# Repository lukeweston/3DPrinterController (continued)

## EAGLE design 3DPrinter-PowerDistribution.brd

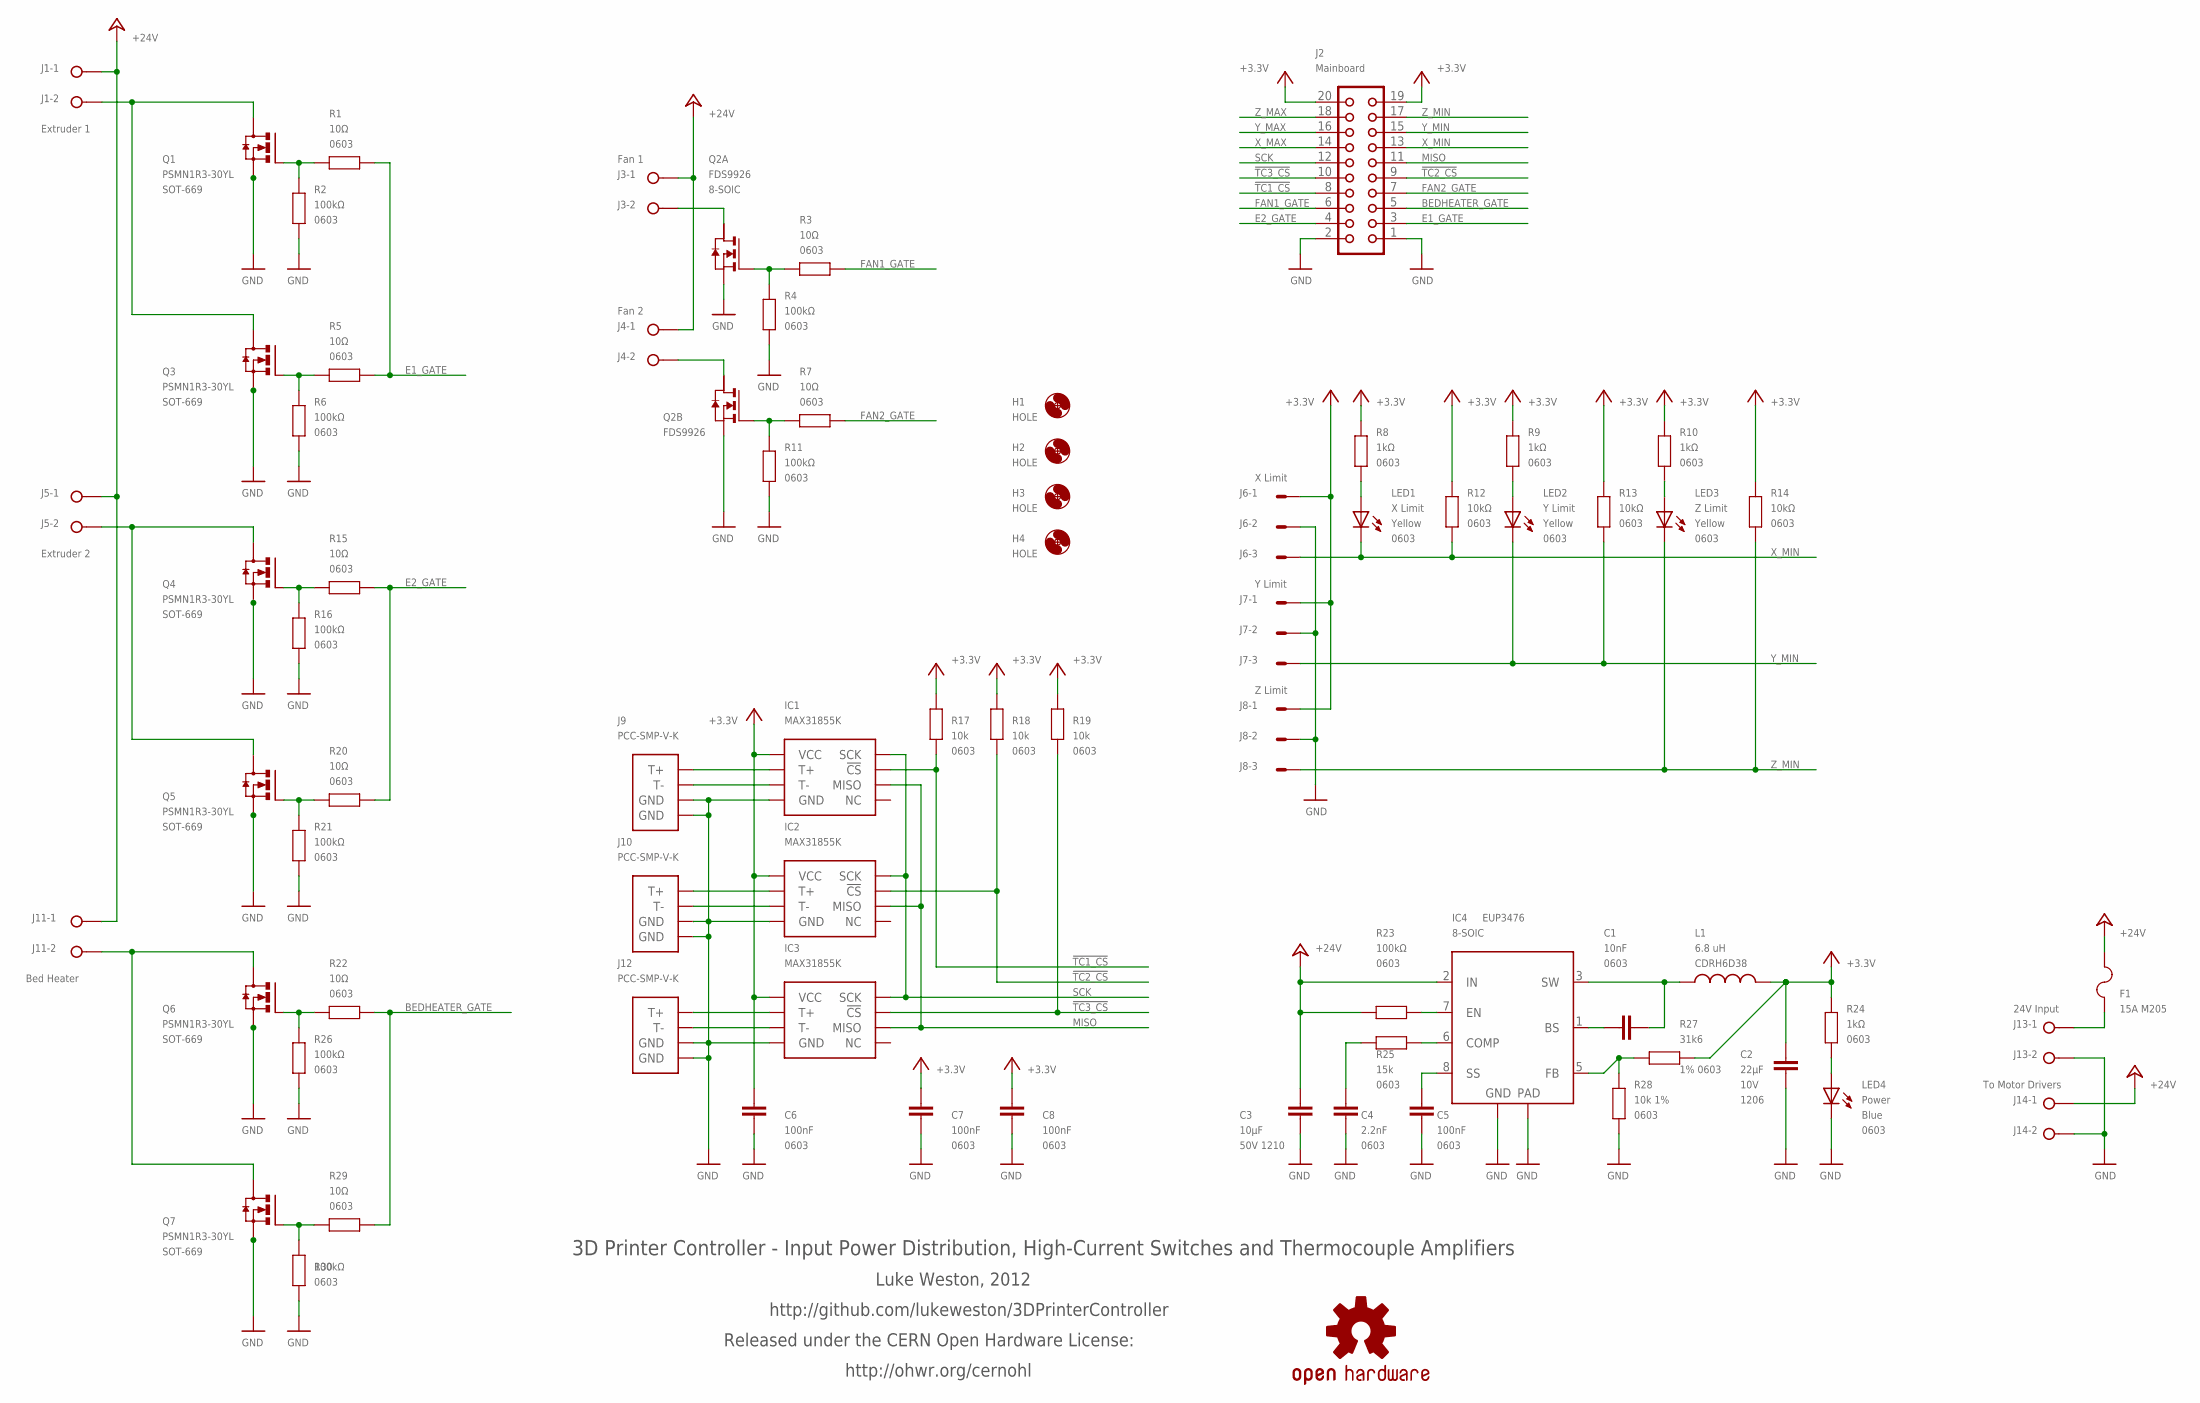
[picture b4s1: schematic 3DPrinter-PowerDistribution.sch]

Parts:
C1: 10nF; 0603
C2: 22µF; C1206K; VOLTAGE 10V
C3: 10µF; C1210K; VOLTAGE 50V 1210
C4: 2.2nF; 0603
C5, C6, C7, C8: 100nF; 0603
F1: 15A M205; SHK20L
H1, H2, H3, H4: HOLE; 3,2
IC1, IC2, IC3: MAX31855K; MCLENG_SOIC-8
IC4: EUP3476; SO08T
J1: Extruder 1; W237-132
J2: Mainboard; CON20L
J3: Fan 1; W237-132
J4: Fan 2; W237-132
J5: Extruder 2; W237-132
J6: X Limit; 7395-03
J7: Y Limit; 7395-03
J8: Z Limit; 7395-03
J9, J10, J12: PCC-SMP-V-K; MCLAUGHLINENG_TC_JACK
J11: Bed Heater; W237-132
J13: 24V Input; W237-132
J14: To Motor Drivers; W237-132
L1: 6.8 uH; CDRH
LED1: X Limit; LED-0603
LED2: Y Limit; LED-0603
LED3: Z Limit; LED-0603
LED4: Power; LED-0603
Q1, Q3, Q4, Q5, Q6, Q7: PSMN1R3-30YL; SOT669
Q2: FDS9926; SM8
R1, R3, R5, R7, R15, R20, R22, R29: 10Ω; 0603
R2, R4, R6, R11, R16, R21, R23, R26, R30: 100kΩ; 0603
R8, R9, R10, R24: 1kΩ; 0603
R12, R13, R14: 10kΩ; 0603
R17, R18, R19: 10k; 0603
R25: 15k; 0603
R27: 31k6; 0603
R28: 10k 1%; 0603
SY: OSHW-LOGOS; OSHW-LOGO-S

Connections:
!TC1_CS: IC1.CS (!CS), J2.8, R17.2
!TC2_CS: IC2.CS (!CS), J2.9, R18.2
!TC3_CS: IC3.CS (!CS), J2.10, R19.2
+3.3V: C2.1, C6.1, C7.1, C8.1, IC1.VCC, IC2.VCC, IC3.VCC, J2.19, J2.20, J6.1, J7.1, J8.1, L1.2, R8.1, R9.1, R10.1, R12.1, R13.1, R14.1, R17.1, R18.1, R19.1, R24.1, R27.1
+24V: C3.1, F1.2A (2), IC4.2 (IN), J1.1, J3.1, J4.1, J5.1, J11.1, J14.1, R23.2
BEDHEATER_GATE: J2.5, R22.1, R29.1
E1_GATE: J2.3, R1.1, R5.1
E2_GATE: J2.4, R15.1, R20.1
FAN1_GATE: J2.6, R3.1
FAN2_GATE: J2.7, R7.1
GND: C2.2, C3.2, C4.1, C5.1, C6.2, C7.2, C8.2, IC1.GND, IC2.GND, IC3.GND, IC4.4 (GND), IC4.9 (TGND), J2.1, J2.2, J6.2, J7.2, J8.2, J9.P$1 (GND), J9.P$2 (GND), J10.P$1 (GND), J10.P$2 (GND), J12.P$1 (GND), J12.P$2 (GND), J13.2, J14.2, LED4.C, Q1.1 (S), Q1.2 (S), Q1.3 (S), Q2.1 (S), Q2.3 (S), Q3.1 (S), Q3.2 (S), Q3.3 (S), Q4.1 (S), Q4.2 (S), Q4.3 (S), Q5.1 (S), Q5.2 (S), Q5.3 (S), Q6.1 (S), Q6.2 (S), Q6.3 (S), Q7.1 (S), Q7.2 (S), Q7.3 (S), R2.2, R4.2, R6.2, R11.2, R16.2, R21.2, R26.2, R28.2, R30.2
J5: J11.2, Q6.MB (D), Q7.MB (D)
MISO: IC1.SO (MISO), IC2.SO (MISO), IC3.SO (MISO), J2.11
unnamed: Q3.4 (G), R5.2, R6.1
unnamed: J1.2, Q1.MB (D), Q3.MB (D)
unnamed: Q4.4 (G), R15.2, R16.1
unnamed: J5.2, Q4.MB (D), Q5.MB (D)
unnamed: Q5.4 (G), R20.2, R21.1
unnamed: F1.1A (1), J13.1
unnamed: Q6.4 (G), R22.2, R26.1
unnamed: IC1.T+, J9.T+
unnamed: Q7.4 (G), R29.2, R30.1
unnamed: J3.2, Q2.5 (D)
unnamed: IC1.T-, J9.T-
unnamed: J4.2, Q2.7 (D)
unnamed: Q2.4 (G), R3.2, R4.1
unnamed: Q2.2 (G), R7.2, R11.1
unnamed: LED1.A, R8.2
unnamed: LED2.A, R9.2
unnamed: LED3.A, R10.2
unnamed: LED4.A, R24.2
unnamed: Q1.4 (G), R1.2, R2.1
unnamed: IC3.T-, J12.T-
unnamed: IC3.T+, J12.T+
unnamed: IC2.T-, J10.T-
unnamed: IC2.T+, J10.T+
unnamed: IC4.7 (EN), R23.1
unnamed: C1.1, IC4.3 (SW), L1.1
unnamed: C1.2, IC4.1 (BS)
unnamed: C4.2, R25.2
unnamed: IC4.6 (COMP), R25.1
unnamed: C5.2, IC4.8 (SS)
unnamed: IC4.5 (FB), R27.2, R28.1
SCK: IC1.SCK, IC2.SCK, IC3.SCK, J2.12
X_MAX: J2.14
X_MIN: J2.13, J6.3, LED1.C, R12.2
Y_MAX: J2.16
Y_MIN: J2.15, J7.3, LED2.C, R13.2
Z_MAX: J2.18
Z_MIN: J2.17, J8.3, LED3.C, R14.2

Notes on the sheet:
3D Printer Controller - Input Power Distribution, High-Current Switches and Thermocouple Amplifiers
Luke Weston, 2012
http://github.com/lukeweston/3DPrinterController
Released under the CERN Open Hardware License:
http://ohwr.org/cernohl

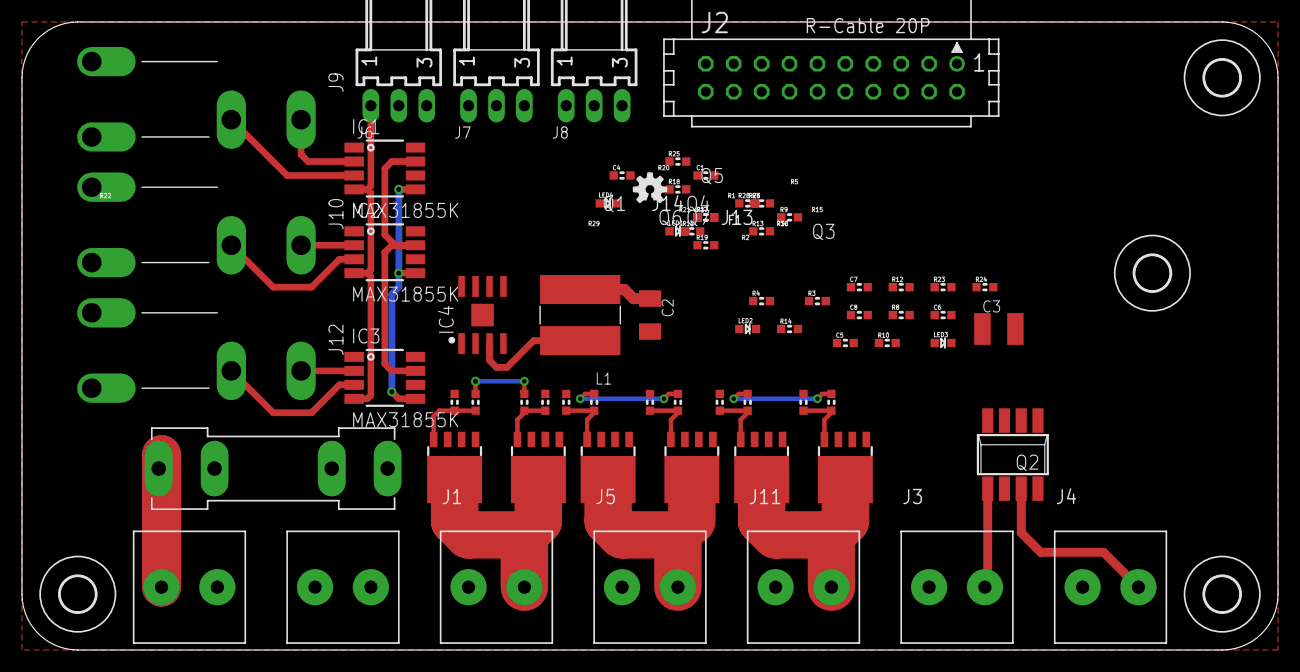
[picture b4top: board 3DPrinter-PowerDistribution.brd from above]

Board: 2 copper layers, 114.3 x 57.1 mm, 74 parts (0 on the bottom side), 47 nets.

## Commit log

2013-04-06 added gerbers
